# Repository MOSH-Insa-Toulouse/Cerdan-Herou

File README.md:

# Cerdan-Herou
Watchdog de température

Ce projet est un système de sécurité. Il permet, connecté à une résistance chauffante de s'éteindre si la température dépasse une valeur fixée par la shield. 

Le code source utilise la rom de l'arduino pour mémoriser les valeurs fixée, un ecran lcd pour afficher les différentes variables, un relais, un thermocouples, un buzzer et une led et un switch encoder. 

Un mode mesure et un mode reset valider en appuyant sur l'encodeur.  

Logigramme: 

mesure de température 
si température > temp set: 
switch du relais
alarme se déclanche 

Demande de reset
reset 

Verifie l'état de l'encodeur
si encodeur change:
fixe une nouvelle valeur de temp set

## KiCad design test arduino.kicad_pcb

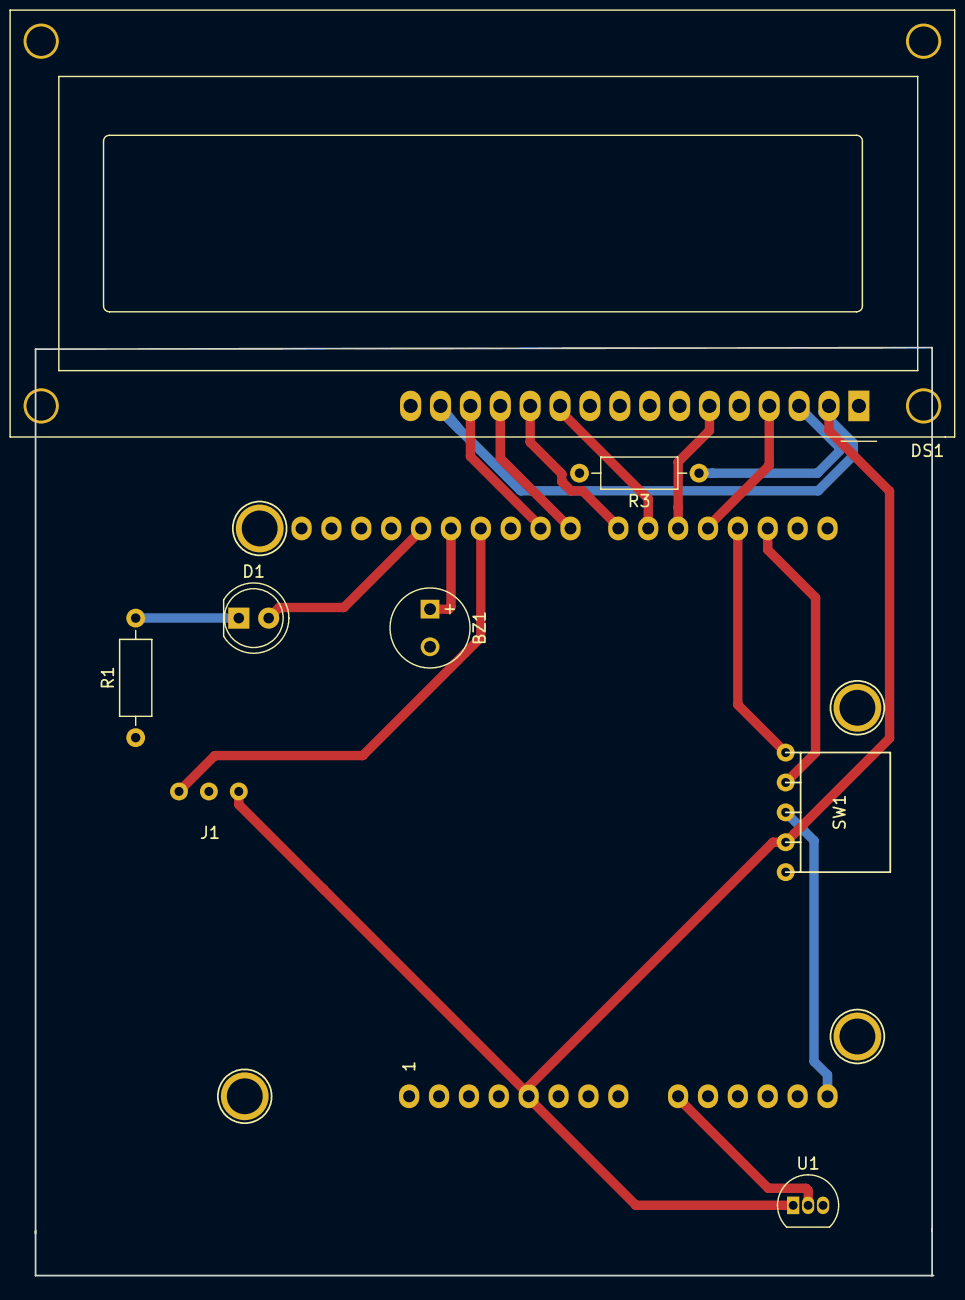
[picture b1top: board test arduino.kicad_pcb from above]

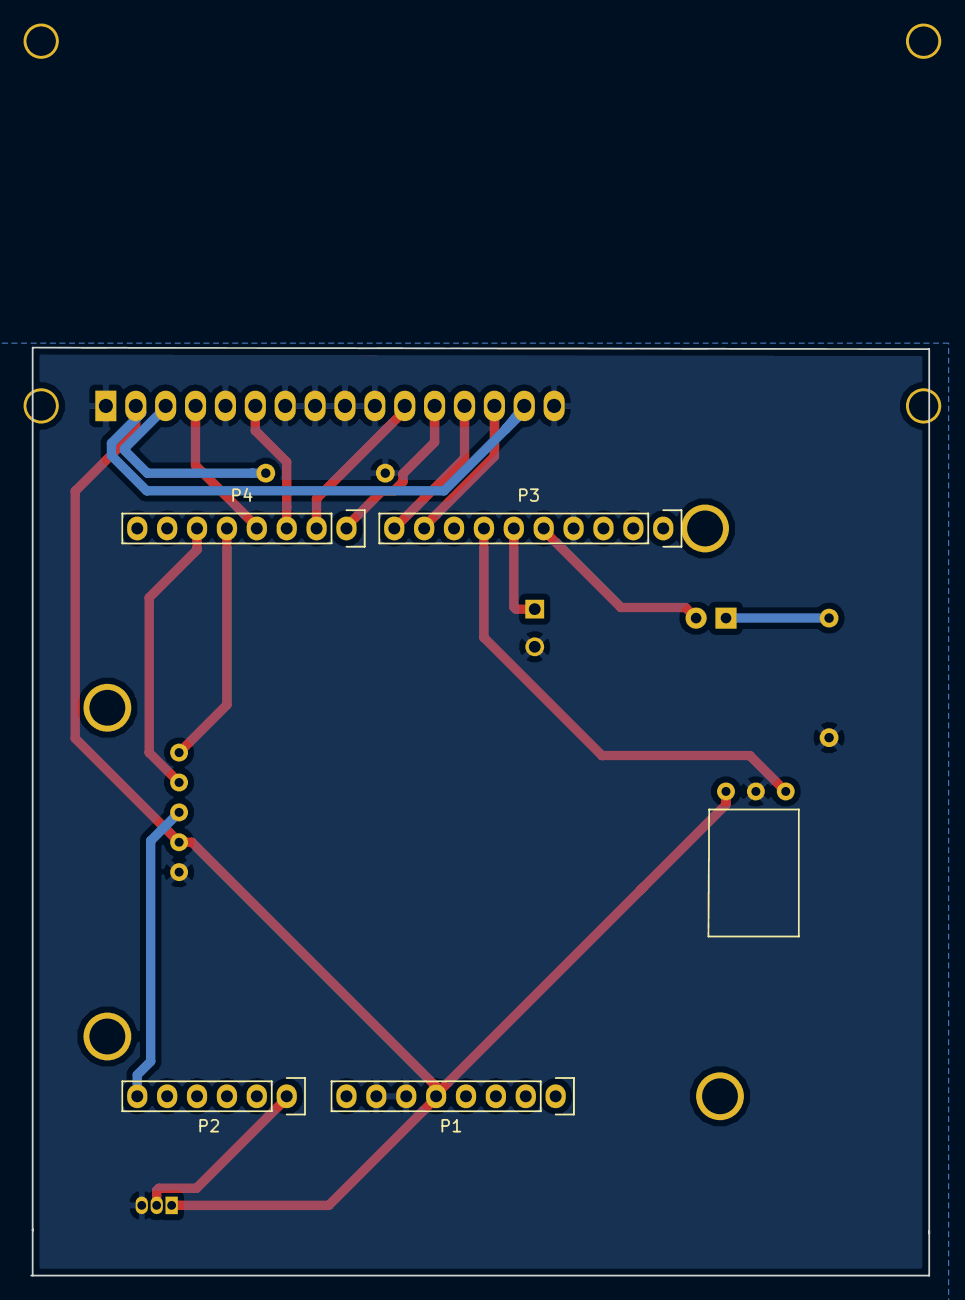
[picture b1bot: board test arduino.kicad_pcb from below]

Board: 2 copper layers, 76.3 x 78.9 mm, 16 parts (4 on the bottom side), 18 nets.

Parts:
BZ1: Buzzer; MagneticBuzzer_Kingstate_KCG0601
D1: LED; LED_D5.0mm
DS1: WC1602A
J1: Conn_01x03_Female; Relais
P1: Power; Socket_Strip_Arduino_1x08
P2: Analog; Socket_Strip_Arduino_1x06
P3: Digital; Socket_Strip_Arduino_1x10
P4: Digital; Socket_Strip_Arduino_1x08
P5, P6, P7, P8: CONN_01X01; Arduino_1pin
R1, R3: R; R_Axial_DIN0207_L6.3mm_D2.5mm_P10.16mm_Horizontal
SW1: Encoder_KY-040; KY-040
U1: TSIC206-TO92; TO-92_Inline

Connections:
+5V: DS1.2, DS1.15, J1.DC+, P1.5, SW1.+, U1.1
/2: P4.6, SW1.B
/3(**): P4.5, SW1.A
/4: DS1.4, P4.4
/5(**): DS1.6, P4.3
/6(**): DS1.11, P4.2
/7: DS1.12, P4.1
/8: DS1.13, P3.10
/9(**): DS1.14, P3.9
/11(**/MOSI): J1.IN, P3.7
/12(MISO): BZ1.1, P3.6
/13(SCK): D1.2, P3.5
/A0: P2.1, U1.2
/A4(SDA): P2.5, P3.2
/A5(SCL): P2.6, P3.1, SW1.SW
GND: BZ1.2, DS1.1, DS1.5, DS1.7, DS1.8, DS1.9, DS1.10, DS1.16, J1.DC-, P1.6, P1.7, P3.4, R1.1, R3.2, SW1.GND, U1.3
unnamed: D1.1, R1.2
unnamed: DS1.3, R3.1
